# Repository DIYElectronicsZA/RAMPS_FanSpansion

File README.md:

# RAMPS_FanSpansion
A small board to allow additional fan control using the RAMPS1.4 platform

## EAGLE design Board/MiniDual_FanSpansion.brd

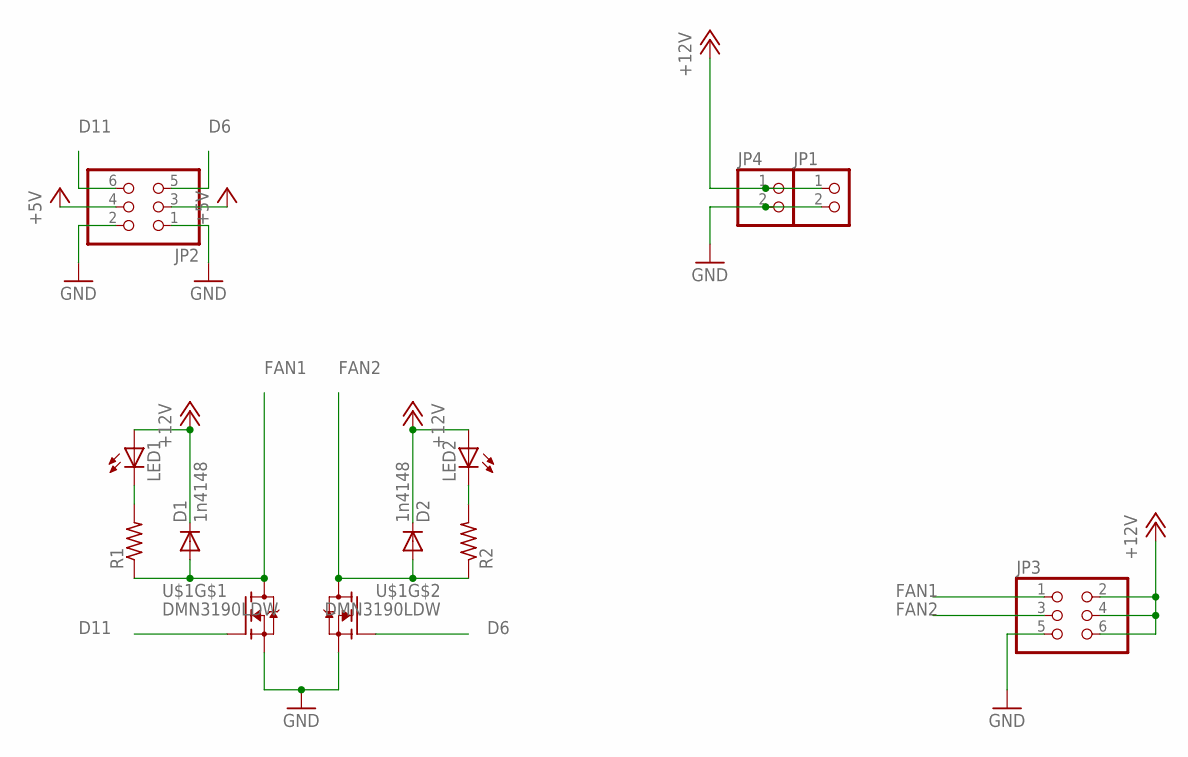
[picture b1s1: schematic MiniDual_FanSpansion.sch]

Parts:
D1, D2: 1n4148; SOD323-R
JP1, JP4: PINHD-1X2; 1X02
JP2, JP3: PINHD-2X3; 2X03
LED1, LED2: LEDSML0805; SML0805
R1, R2: R-US_R0805; R0805
U$1: DMN3190LDW; SOT65P210X110-6N

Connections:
+5V: JP2.3, JP2.4
+12V: D1.C, D2.C, JP1.1, JP3.2, JP3.4, JP3.6, JP4.1, LED1.A, LED2.A
D6: JP2.5, U$1.2 (G)
D11: JP2.6, U$1.5 (G)
FAN1: D1.A, JP3.1, R1.1, U$1.3 (D)
FAN2: D2.A, JP3.3, R2.1, U$1.6 (D)
GND: JP1.2, JP2.1, JP2.2, JP3.5, JP4.2, U$1.1 (S), U$1.4 (S)
unnamed: LED1.C, R1.2
unnamed: LED2.C, R2.2

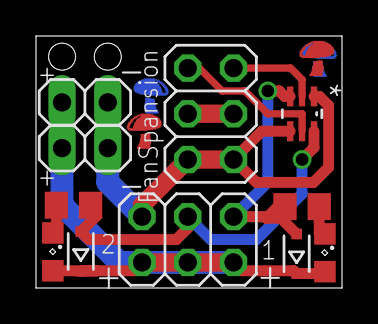
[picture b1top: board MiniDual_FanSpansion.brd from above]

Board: 2 copper layers, 17.0 x 14.0 mm, 11 parts (0 on the bottom side), 9 nets.

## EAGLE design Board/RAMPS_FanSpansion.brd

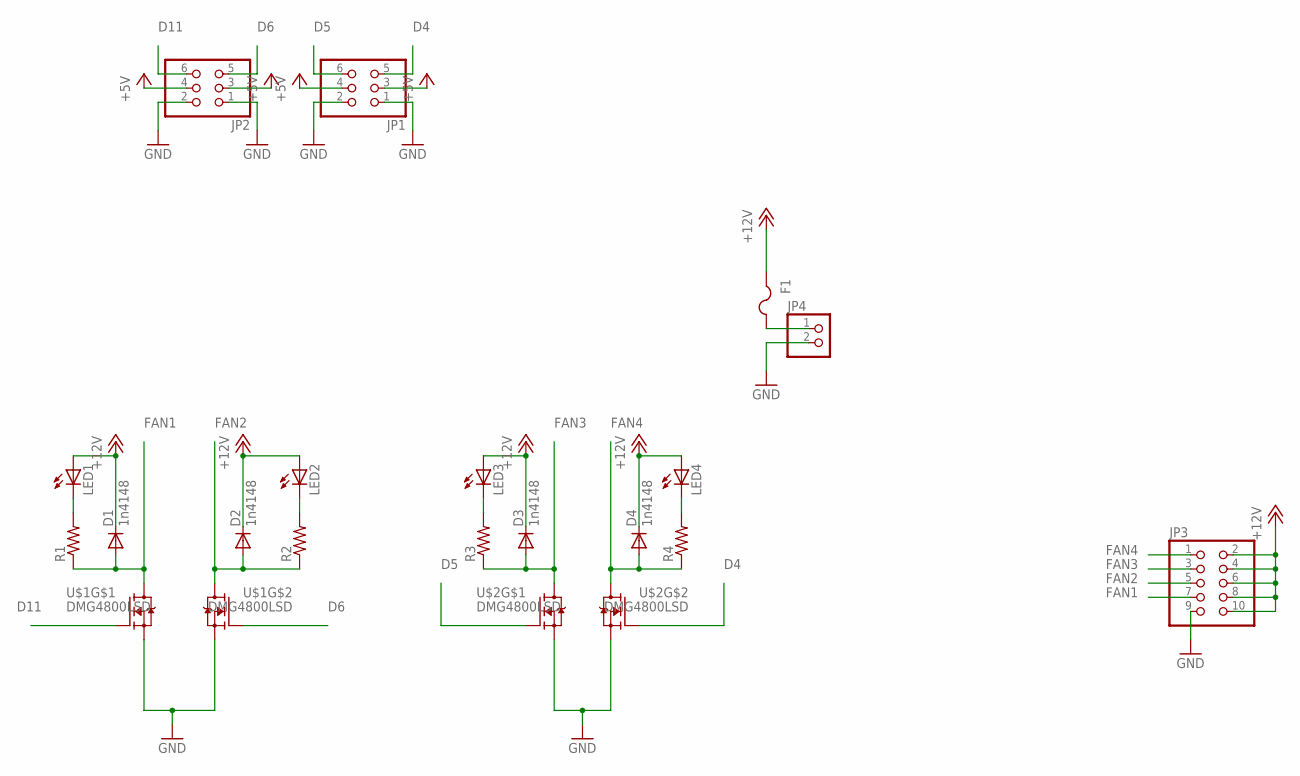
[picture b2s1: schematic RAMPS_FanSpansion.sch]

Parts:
D1, D2, D3, D4: 1n4148; SOD323-R
F1: PTCFUSE-1812; 1812
JP1, JP2: PINHD-2X3; 2X03
JP3: PINHD-2X5; 2X05
JP4: PINHD-1X2; 1X02
LED1, LED2, LED3, LED4: LEDSML0805; SML0805
R1, R2, R3, R4: R-US_R0805; R0805
U$1, U$2: DMG4800LSD; SO08

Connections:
+5V: JP1.3, JP1.4, JP2.3, JP2.4
+12V: D1.C, D2.C, D3.C, D4.C, F1.1, JP3.2, JP3.4, JP3.6, JP3.8, JP3.10, LED1.A, LED2.A, LED3.A, LED4.A
D4: JP1.5, U$2.4 (G)
D5: JP1.6, U$2.2 (G)
D6: JP2.5, U$1.4 (G)
D11: JP2.6, U$1.2 (G)
FAN1: D1.A, JP3.7, R1.1, U$1.7 (D), U$1.8 (D)
FAN2: D2.A, JP3.5, R2.1, U$1.5 (D), U$1.6 (D)
FAN3: D3.A, JP3.3, R3.1, U$2.7 (D), U$2.8 (D)
FAN4: D4.A, JP3.1, R4.1, U$2.5 (D), U$2.6 (D)
GND: JP1.1, JP1.2, JP2.1, JP2.2, JP3.9, JP4.2, U$1.1 (S), U$1.3 (S), U$2.1 (S), U$2.3 (S)
unnamed: LED1.C, R1.2
unnamed: LED2.C, R2.2
unnamed: LED3.C, R3.2
unnamed: LED4.C, R4.2
unnamed: F1.2, JP4.1

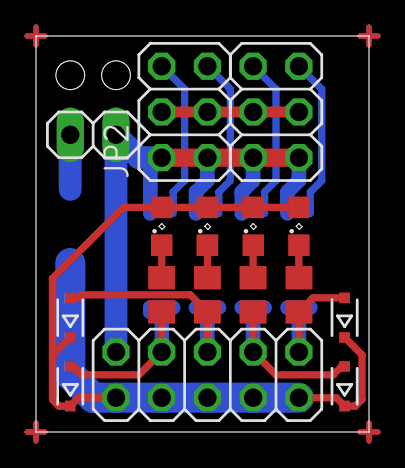
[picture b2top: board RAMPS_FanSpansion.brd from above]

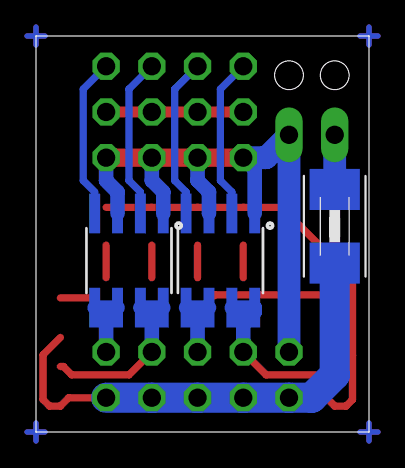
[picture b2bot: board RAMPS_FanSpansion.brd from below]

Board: 2 copper layers, 18.5 x 22.0 mm, 19 parts (3 on the bottom side), 16 nets.

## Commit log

2016-05-31 Exported PDFs
2016-06-01 Designed Mini Board
2016-09-22 sync
